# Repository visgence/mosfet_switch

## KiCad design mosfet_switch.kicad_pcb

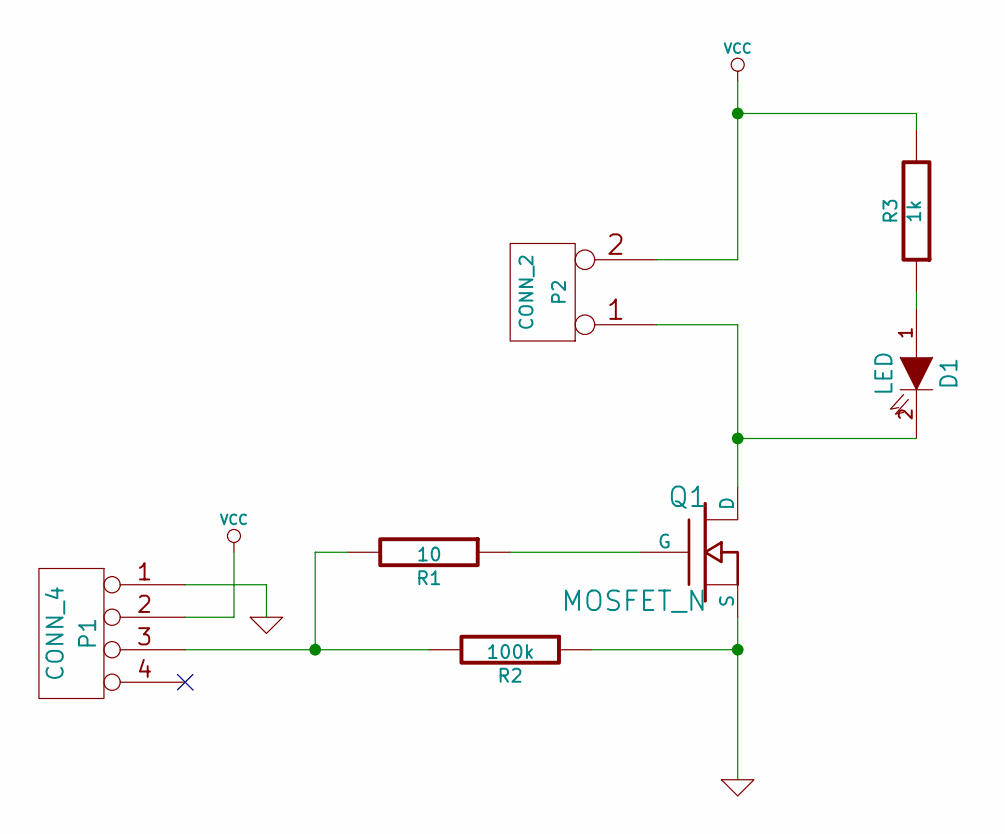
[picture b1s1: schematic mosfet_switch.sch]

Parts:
D1: LED; LED-5MM
P1: CONN_4; bornier4
P2: CONN_2; bornier2
Q1: MOSFET_N; TO-220_FET-GDS_Vertical
R1: 10; R4
R2: 100k; R4
R3: 1k; R4

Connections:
GND: P1.1, Q1.S, R2.1
unnamed: D1.1 (A), R3.1
unnamed: D1.2 (K), P2.1, Q1.D
unnamed: P1.3, R1.2, R2.2
unnamed: Q1.G, R1.1
VCC: P1.2, P2.2 (PM), R3.2

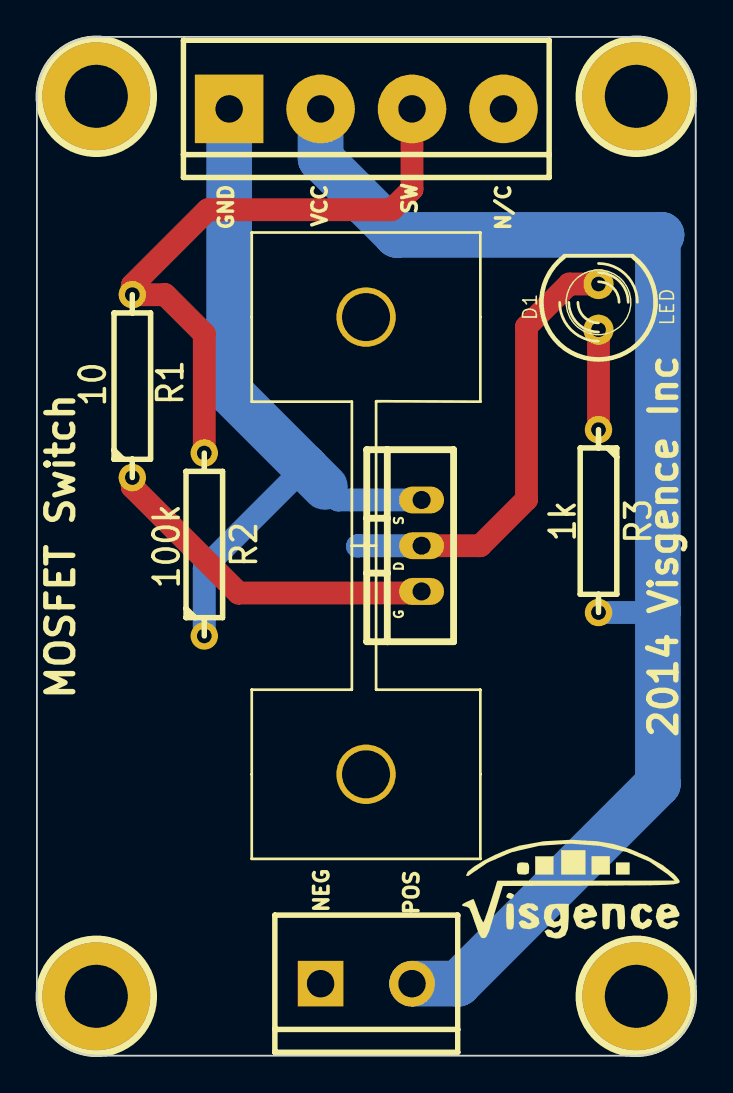
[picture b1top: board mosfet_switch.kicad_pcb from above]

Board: 2 copper layers, 36.6 x 56.6 mm, 12 parts (0 on the bottom side), 6 nets.

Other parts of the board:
EV-T220: VAL**; EV-T220
h?: pin; 1pin_C
h?#2, h?#3, h?#4: pin; 1pin_C

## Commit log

2016-06-01 Found or made all the pieces for the Mosfet board and assembled them in KiCad.
